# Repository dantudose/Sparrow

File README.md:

# Sparrow

## Arduino-compatible IoT sensor node made from two boards: the Node and the Nest - used for programming and debugging.

Features include:

* Atmega128RFA1 8-bit AVR low-power microcontroller
* Integrated 2.4GHz radio transceiver
* Precision temperature & humidity sensor
* Barometer/altimeter
* Light sensor (visible, IR and UV spectrum, luxmeter and UV radiation index)
* High capacity CR2450 battery holder
* Fully-compatible with Arduino, with dedicated libraries for easy programming of the sensors and radio.

## Repository Contents

* **/Hardware** - Eagle design files (.brd, .sch)
* **/Images** - Board images
* **/bin** - Binaries (board bootloader)

## Programming

### Installing Arduino Libraries and Boad Configs

1. Open the Arduino IDE
2. Go to File → Preferences
3. In the Additional Boards Manager URLs textbox add the following link: http://clkdiv8.com/download/package_clkdiv8pre_index.json
4. Close the window by pressing OK
5. Go to Tools → Board → Boards Manager
6. Search “sparrow”
7. Hit Install
8. You're done!

### Tutorials

Most tutorials for using the on-board sensors or radio are available <a href="https://clkdiv8.com/wiki/doku.php/tutorials">here</a>.

### Bootloader
The board comes pre-loaded with a bootloader. Should you need to re-write it, connect an AVR-ISP or JTAG to the corresponding port and burn the <a href="https://github.com/dantudose/Sparrow/blob/main/Node/bin/">bootloader</a> .hex file with _atmega128rfa1_ as a target and the following fuse settings:

<table>
<thead>
  <tr>
    <th>Fuse</th>
    <th>Value</th>
  </tr>
</thead>
<tbody>
  <tr>
    <td>HIGH</td>
    <td>0xD0</td>
  </tr>
  <tr>
    <td>LOW</td>
    <td>0xF7</td>
  </tr>
  <tr>
    <td>EXT</td>
    <td>0XFE</td>
  </tr>
</tbody>
</table>

## Pinout and Sensor Addresses

<table><thead>
  <tr>
    <th></th>
    <th>GPIO Pin</th>
    <th>Arduino Pin</th>
    <th></th>
    <th>Sensor</th>
    <th>I2C Address</th>
  </tr></thead>
<tbody>
  <tr>
    <td>LED R</td>
    <td>PB4</td>
    <td>8</td>
    <td></td>
    <td>Si1145</td>
    <td>0x60</td>
  </tr>
  <tr>
    <td>LED G</td>
    <td>PB5</td>
    <td>11</td>
    <td></td>
    <td>Si7020</td>
    <td>0x40</td>
  </tr>
  <tr>
    <td>LED B</td>
    <td>PB6</td>
    <td>10</td>
    <td></td>
    <td>MS5637</td>
    <td>0x76</td>
  </tr>
  <tr>
    <td>Sensor <br>Enable <br> (Active LOW)</td>
    <td>PE7</td>
    <td>19</td>
    <td></td>
    <td></td>
    <td></td>
  </tr>
  <tr>
    <td>Battery<br>Level</td>
    <td>PF0</td>
    <td>A0</td>
    <td></td>
    <td></td>
    <td></td>
  </tr>
</tbody>
</table>

## License Information

This product is _**open source**_! 

Please review the LICENSE file for license information.

Distributed as-is; no warranty is given.

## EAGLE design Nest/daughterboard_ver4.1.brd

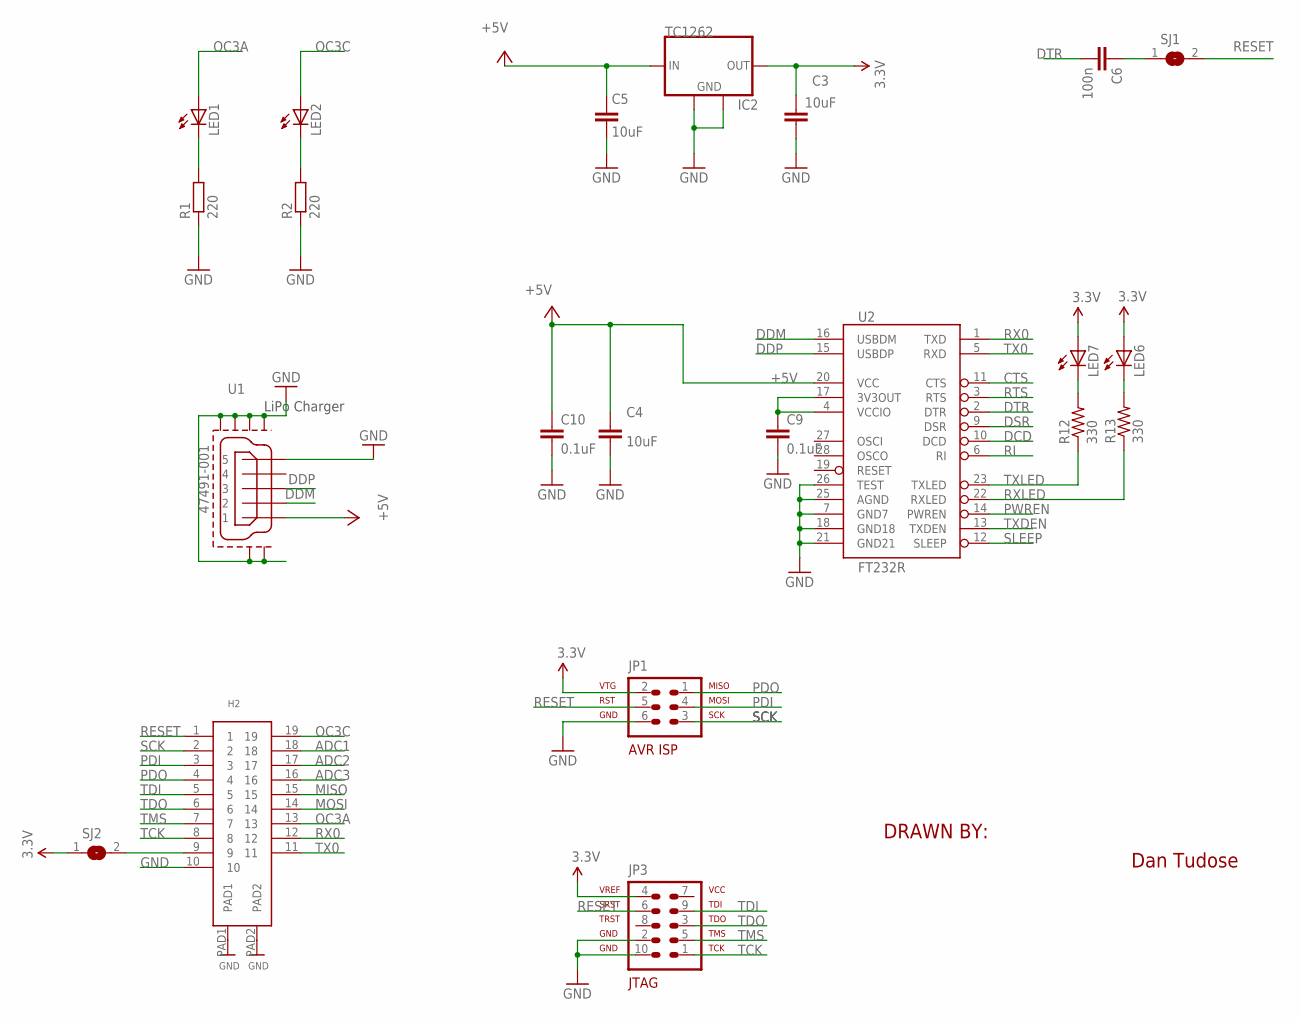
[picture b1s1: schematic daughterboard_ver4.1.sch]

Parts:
C3, C4, C5: 10uF; C0402
C6: 100n; C0402
C9, C10: 0.1uF; 0402-CAP
H2: DF9-19P-1V(32)
IC2: TC1262; SOT223
JP1: AVR-ISP-6SMD; 2X3SMD
JP3: AVR-JTAG-10
LED1, LED2: LEDCHIPLED_0603; CHIPLED_0603
LED6, LED7: LEDCHIP-LED0603; CHIP-LED0603
R1, R2: 220; R0402
R12, R13: 330; 0402-RES
SJ1, SJ2: SJ
U1: 47491-001; 47491-0001
U2: FT232R; SSOP28DB

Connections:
3.3V: C3.1, IC2.3 (OUT), JP1.2, JP3.4, LED6.A, LED7.A, SJ2.1
+5V: C4.1, C5.1, C10.1, IC2.1 (IN), U1.1, U2.20 (VCC)
ADC1: H2.18
ADC2: H2.17
ADC3: H2.16
CTS: U2.11 (CTS)
DCD: U2.10 (DCD)
DDM: U1.2, U2.16 (USBDM)
DDP: U1.3, U2.15 (USBDP)
DSR: U2.9 (DSR)
DTR: C6.2, U2.2 (DTR)
GND: C3.2, C4.2, C5.2, C9.2, C10.2, H2.10, H2.PAD1, H2.PAD2, IC2.2 (GND), IC2.4 (GND), JP1.6, JP3.2, JP3.10, R1.1, R2.1, U1.5, U1.GND1, U1.GND2, U1.GND3, U1.GND4, U1.GND5, U1.GND6, U2.7 (GND7), U2.18 (GND18), U2.21 (GND21), U2.25 (AGND), U2.26 (TEST)
MISO: H2.15
MOSI: H2.14
unnamed: LED7.C, R12.2
unnamed: LED6.C, R13.2
unnamed: H2.9, SJ2.2
unnamed: LED1.C, R1.2
unnamed: LED2.C, R2.2
unnamed: C9.1, U2.4 (VCCIO), U2.17 (3V3OUT)
unnamed: C6.1, SJ1.1
OC3A: H2.13, LED1.A
OC3C: H2.19, LED2.A
PDI: H2.3, JP1.4
PDO: H2.4, JP1.1
PWREN: U2.14 (PWREN)
RESET: H2.1, JP1.5, JP3.6, SJ1.2
RI: U2.6 (RI)
RTS: U2.3 (RTS)
RX0: H2.12, U2.1 (TXD)
RXLED: R13.1, U2.22 (RXLED)
SCK: H2.2, JP1.3
SLEEP: U2.12 (SLEEP)
TCK: H2.8, JP3.1
TDI: H2.5, JP3.9
TDO: H2.6, JP3.3
TMS: H2.7, JP3.5
TX0: H2.11, U2.5 (RXD)
TXDEN: U2.13 (TXDEN)
TXLED: R12.1, U2.23 (TXLED)

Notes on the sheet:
LiPo Charger
DRAWN BY:
Dan Tudose

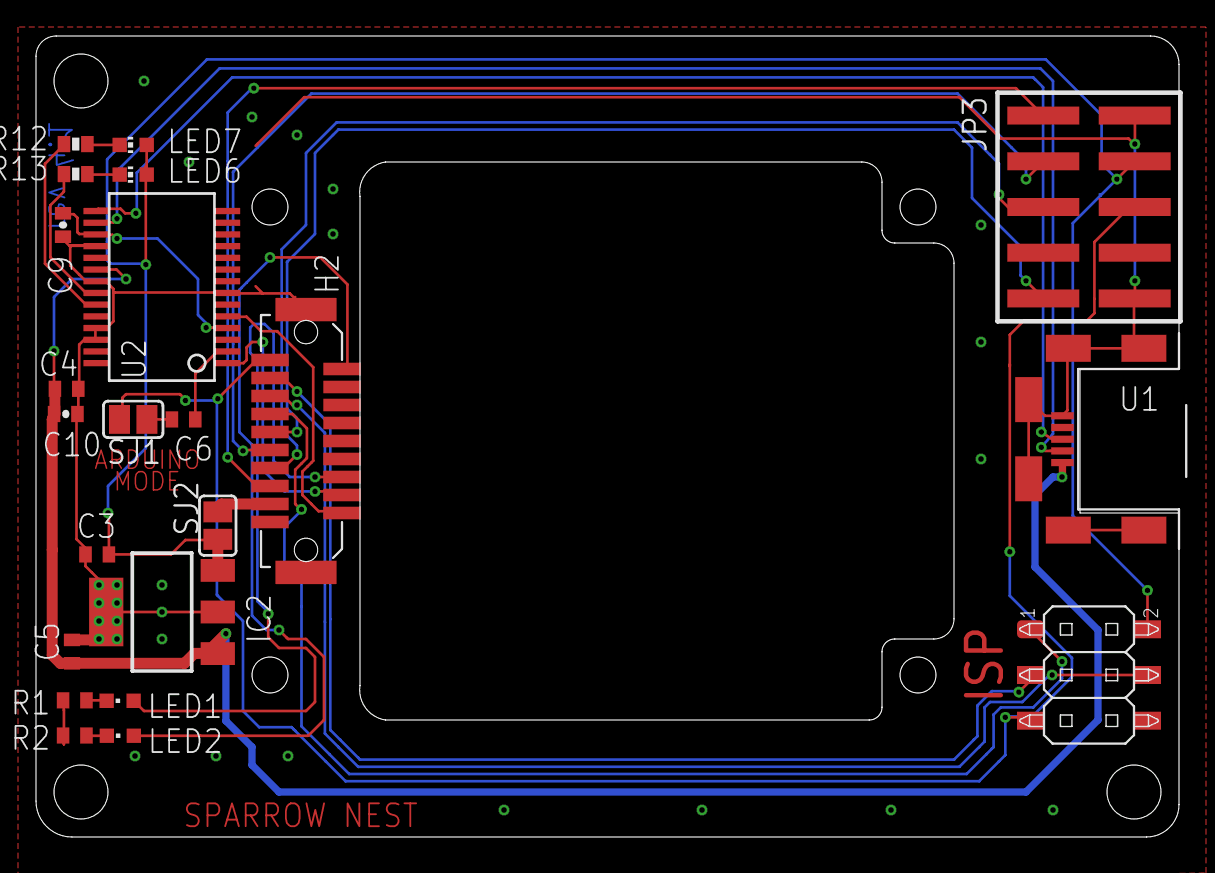
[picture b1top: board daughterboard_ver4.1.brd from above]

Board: 2 copper layers, 63.5 x 44.5 mm, 22 parts (0 on the bottom side), 27 nets.

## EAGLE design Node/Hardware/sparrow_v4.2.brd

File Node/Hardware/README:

Eagle (Fusion360) files and schematic in pdf format.

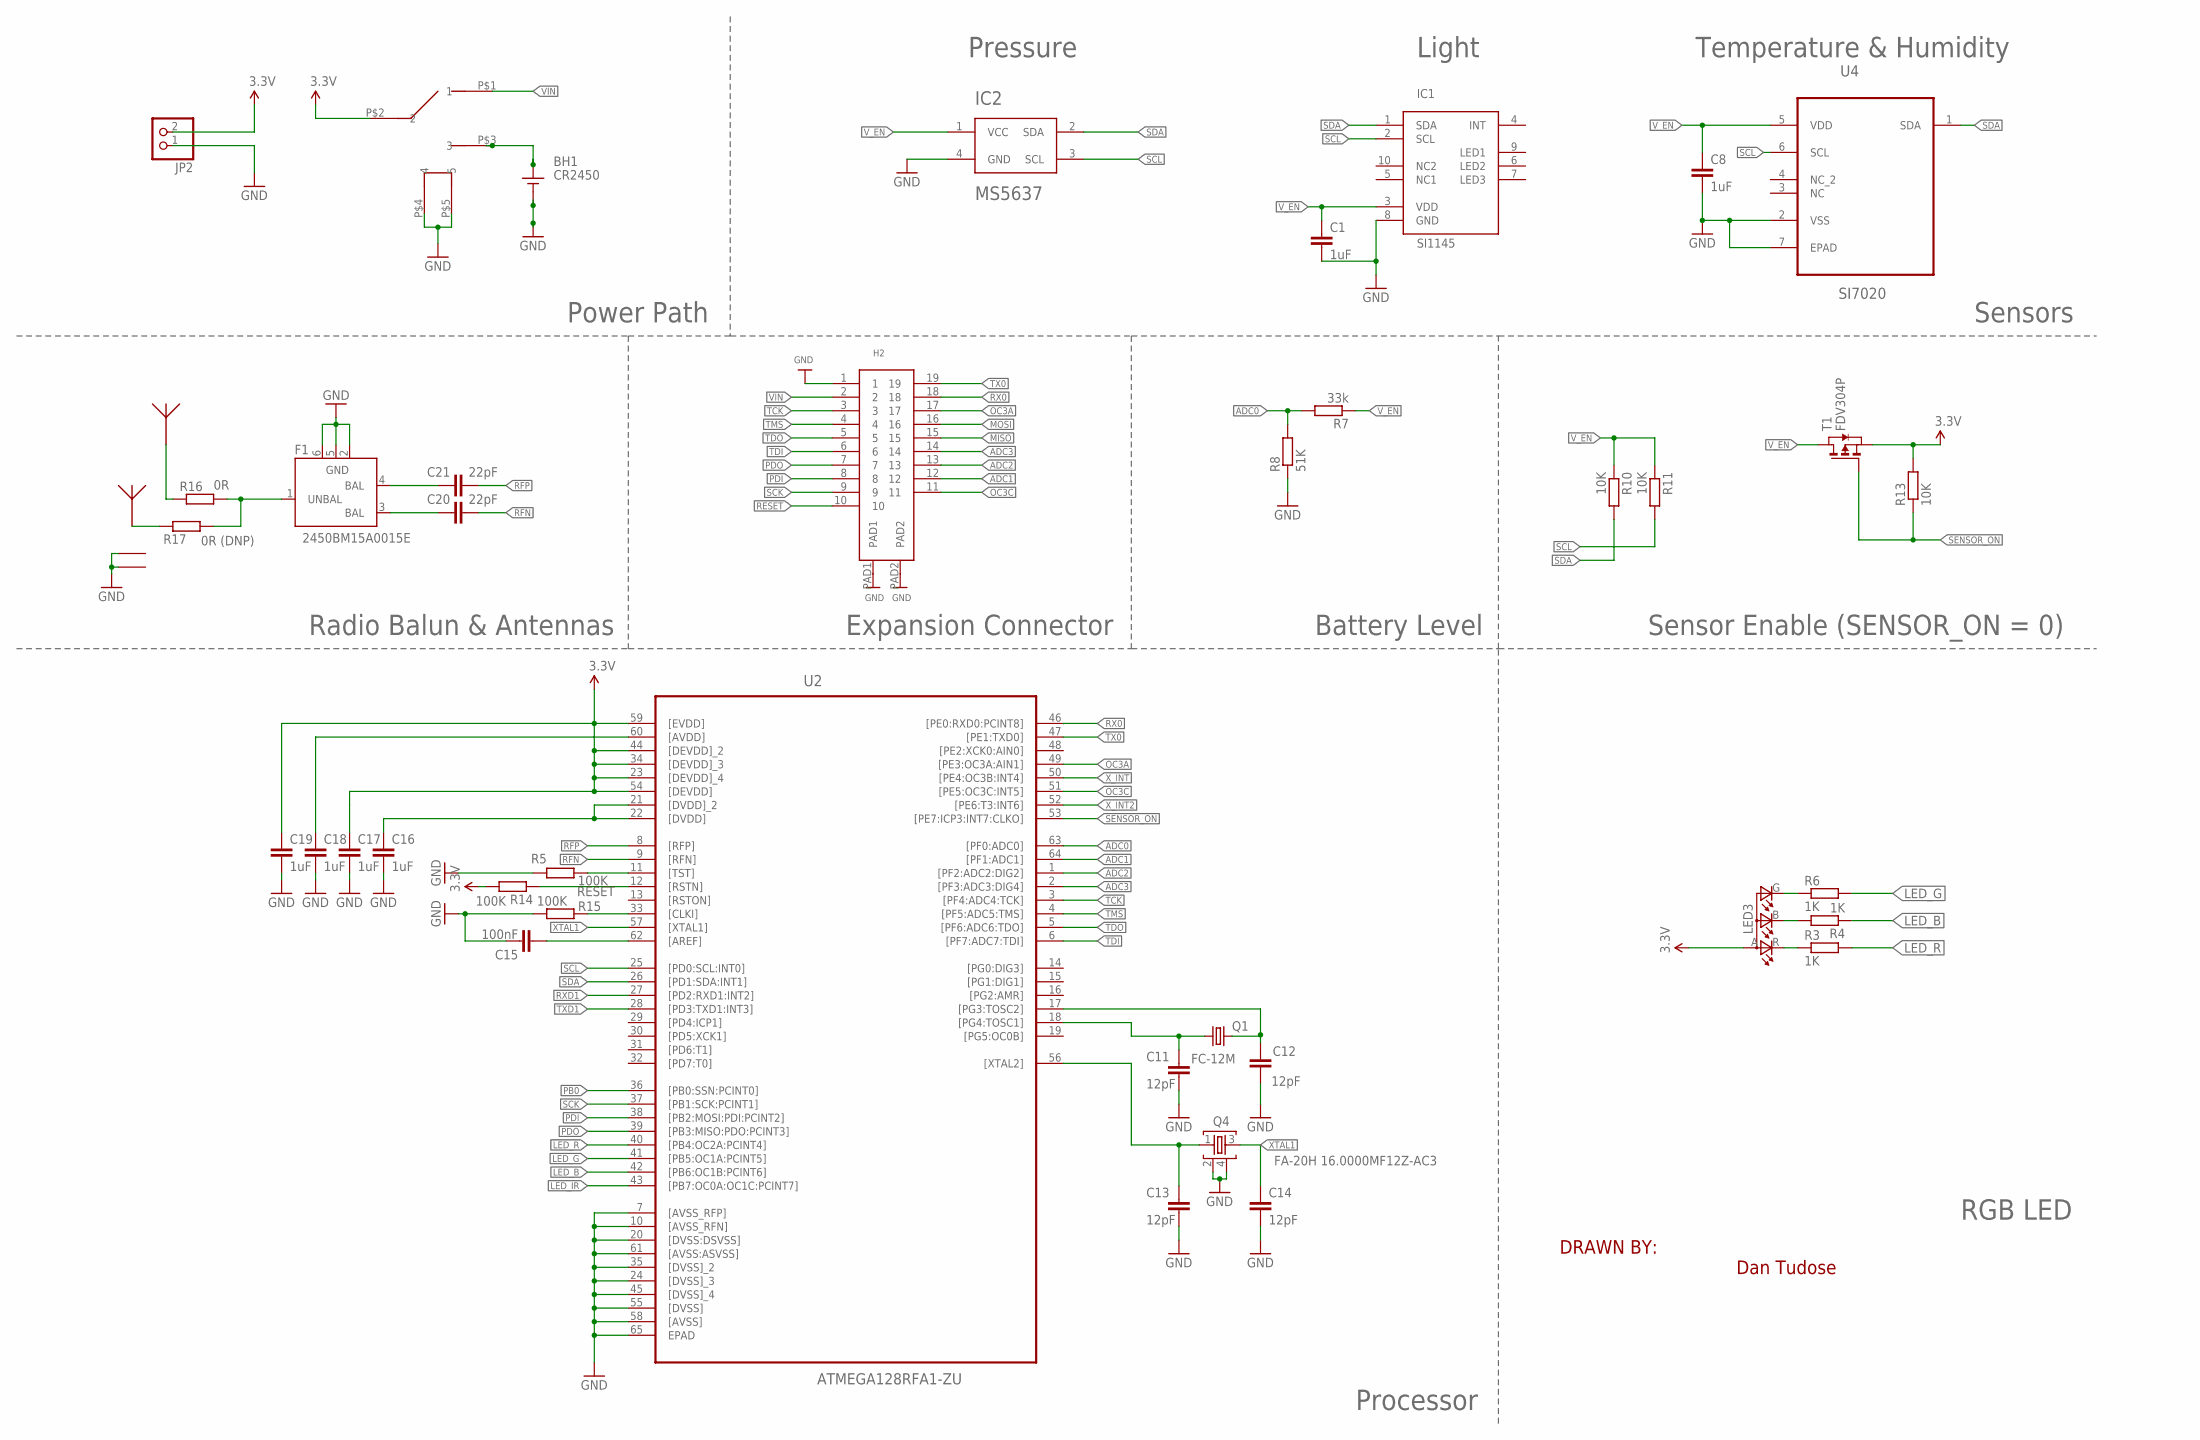
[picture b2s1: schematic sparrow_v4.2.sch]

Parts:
C1, C8, C16, C17, C18, C19: 1uF; C0402
C11, C12, C13, C14: 12pF; C0402
C15: 100nF; C0402
C20, C21: 22pF; C0402
F1: 2450BM15A0015E; 2450BM15A0002
H2: DF9-19P-1V(32)
IC1: SI1145; QFN10
IC2: MS5637
JP2: PINHD-1X2; 1X02
LED3: LED_RGB_CREE_PLCC4; P-LCC-4-4
Q1: FC-12M
Q4: FA-20H 16.0000MF12Z-AC3; FA-20H
R3, R4, R6: 1K; R0402
R5, R14, R15: 100K; R0402
R7: 33k; R0402
R8: 51K; R0402
R10, R11, R13: 10K; R0402
R16: 0R; R0402
R17: 0R (DNP); R0402
T1: FDV304P; SOT-23
U1: SMTU2450N-LF; BATPACK
U2: ATMEGA128RFA1-ZU; QFN50P900X900X90-64N
U4: SI7020; DFN300X300X110-7N
U8: ANTENNA; ANTPACK
U10: UFL-R-SMT; U.FLPACK
U$1: SWITCH; PCM12

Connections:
3.3V: C17.1, C19.1, JP2.2, LED3.A (A2), R13.2, R14.2, T1.2 (S), U2.23 ([DEVDD]_4), U2.34 ([DEVDD]_3), U2.44 ([DEVDD]_2), U2.54 ([DEVDD]), U2.59 ([EVDD]), U$1.P$2 (2)
ADC0: R7.2, R8.2, U2.63 ([PF0:ADC0])
ADC1: H2.12, U2.64 ([PF1:ADC1])
ADC2: H2.13, U2.1 ([PF2:ADC2:DIG2])
ADC3: H2.14, U2.2 ([PF3:ADC3:DIG4])
GND: C1.2, C8.2, C11.2, C12.2, C13.2, C14.2, C15.1, C16.2, C17.2, C18.2, C19.2, F1.2 (GND), F1.5 (GND), F1.6 (GND), H2.1, H2.PAD1, H2.PAD2, IC1.8 (GND), IC2.4 (GND), JP2.1, Q4.2, Q4.4, R5.2, R8.1, R15.2, U1.P$2, U2.7 ([AVSS_RFP]), U2.10 ([AVSS_RFN]), U2.20 ([DVSS:DSVSS]), U2.24 ([DVSS]_3), U2.35 ([DVSS]_2), U2.45 ([DVSS]_4), U2.55 ([DVSS]), U2.58 ([AVSS]), U2.61 ([AVSS:ASVSS]), U2.65 (EPAD), U4.2 (VSS), U4.7 (EPAD), U10.GND1, U10.GND2, U$1.P$4 (4), U$1.P$5 (5)
LED_B: R4.1, U2.42 ([PB6:OC1B:PCINT6])
LED_G: R6.2, U2.41 ([PB5:OC1A:PCINT5])
LED_IR: U2.43 ([PB7:OC0A:OC1C:PCINT7])
LED_R: R3.2, U2.40 ([PB4:OC2A:PCINT4])
MISO: H2.15
MOSI: H2.16
unnamed: U1.P$1, U$1.P$3 (3)
unnamed: C16.1, U2.21 ([DVDD]_2), U2.22 ([DVDD])
unnamed: LED3.R (CRED), R3.1
unnamed: C12.1, Q1.2, U2.17 ([PG3:TOSC2])
unnamed: C11.1, Q1.1, U2.18 ([PG4:TOSC1])
unnamed: LED3.B (CBLUE), R4.2
unnamed: LED3.G (CGREEN), R6.1
unnamed: C18.1, U2.60 ([AVDD])
unnamed: R5.1, U2.11 ([TST])
unnamed: C13.1, Q4.1, U2.56 ([XTAL2])
unnamed: R15.1, U2.33 ([CLKI])
unnamed: C15.2, U2.62 ([AREF])
unnamed: C20.1, F1.3 (BAL)
unnamed: C21.1, F1.4 (BAL)
unnamed: F1.1 (UNBAL), R16.2, R17.1
unnamed: R16.1, U8.P$1
unnamed: R17.2, U10.P$1
OC3A: H2.17, U2.49 ([PE3:OC3A:AIN1])
OC3C: H2.11, U2.51 ([PE5:OC3C:INT5])
PB0: U2.36 ([PB0:SSN:PCINT0])
PDI: H2.8, U2.38 ([PB2:MOSI:PDI:PCINT2])
PDO: H2.7, U2.39 ([PB3:MISO:PDO:PCINT3])
RESET: H2.10, R14.1, U2.12 ([RSTN])
RFN: C20.2, U2.9 ([RFN])
RFP: C21.2, U2.8 ([RFP])
RX0: H2.18, U2.46 ([PE0:RXD0:PCINT8])
RXD1: U2.27 ([PD2:RXD1:INT2])
SCK: H2.9, U2.37 ([PB1:SCK:PCINT1])
SCL: IC1.2 (SCL), IC2.3 (SCL), R11.2, U2.25 ([PD0:SCL:INT0]), U4.6 (SCL)
SDA: IC1.1 (SDA), IC2.2 (SDA), R10.2, U2.26 ([PD1:SDA:INT1]), U4.1 (SDA)
SENSOR_ON: R13.1, T1.3 (G), U2.53 ([PE7:ICP3:INT7:CLKO])
TCK: H2.3, U2.3 ([PF4:ADC4:TCK])
TDI: H2.6, U2.6 ([PF7:ADC7:TDI])
TDO: H2.5, U2.5 ([PF6:ADC6:TDO])
TMS: H2.4, U2.4 ([PF5:ADC5:TMS])
TX0: H2.19, U2.47 ([PE1:TXD0])
TXD1: U2.28 ([PD3:TXD1:INT3])
VIN: H2.2, U$1.P$1 (1)
V_EN: C1.1, C8.1, IC1.3 (VDD), IC2.1 (VCC), R7.1, R10.1, R11.1, T1.1 (D), U4.5 (VDD)
XTAL1: C14.1, Q4.3, U2.57 ([XTAL1])
X_INT: U2.50 ([PE4:OC3B:INT4])
X_INT2: U2.52 ([PE6:T3:INT6])

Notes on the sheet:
DRAWN BY:
Dan Tudose
CR2450
BH1
Sensor Enable (SENSOR_ON = 0)
Sensors
Battery Level
RGB LED
Expansion Connector
Radio Balun & Antennas
Power Path
Processor
Pressure
Light
Temperature & Humidity

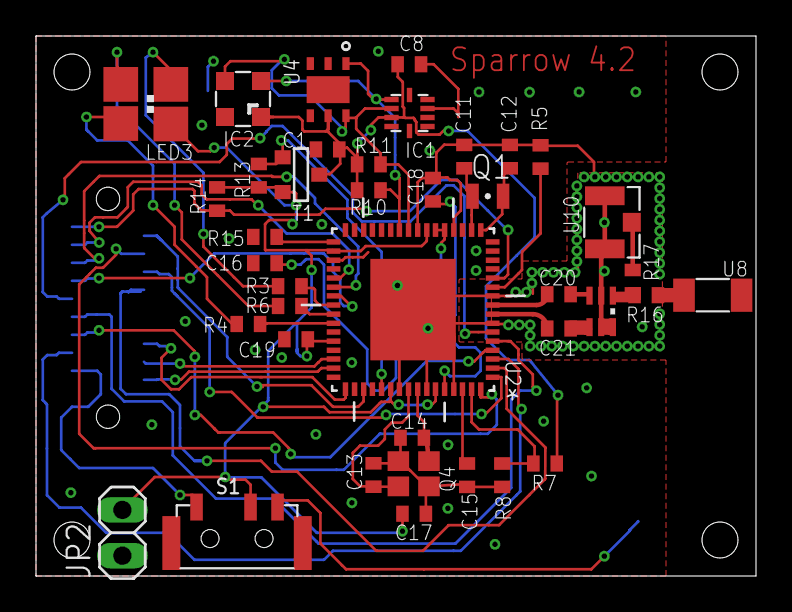
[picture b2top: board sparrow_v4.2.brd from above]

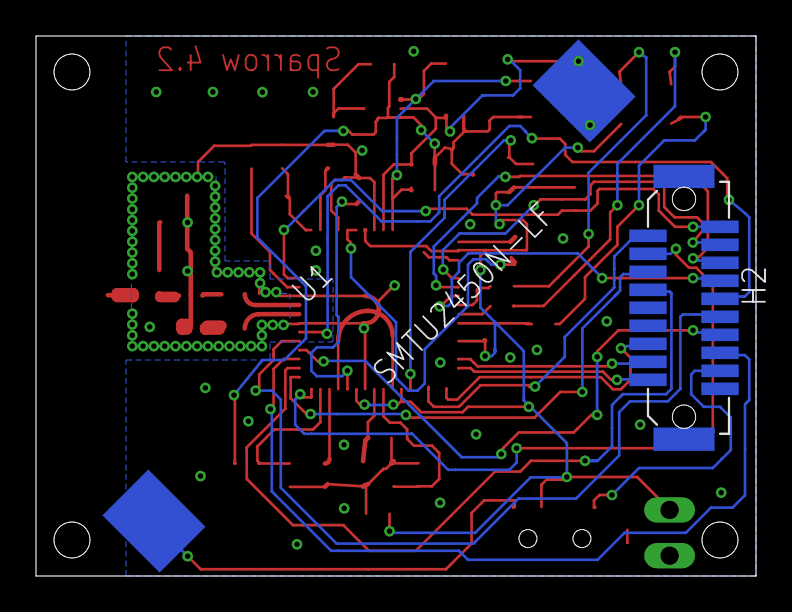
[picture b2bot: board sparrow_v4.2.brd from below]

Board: 2 copper layers, 40.0 x 30.0 mm, 41 parts (2 on the bottom side), 46 nets.
